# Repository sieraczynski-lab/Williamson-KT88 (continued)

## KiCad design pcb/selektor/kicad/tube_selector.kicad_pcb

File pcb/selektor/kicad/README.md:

# TubeSel v0.5: selektor 4 wejść + drabinka przekaźnikowa 63 dB + sterownik I²C

Projekt KiCad 8 (otwiera się też w KiCad 9 i nowszych).

## Zawartość
- `tube_selector.kicad_pro`: projekt (klasy sieci Audio 0,4 mm / Coil 0,3 mm)
- `tube_selector.kicad_sch`: schemat (A3)
- `tube_selector.kicad_pcb`: płytka 96 × 74 mm, 2 warstwy, elementy rozmieszczone, strefy mas na obu warstwach, **bez ścieżek**
- `TubeSel.kicad_sym` + `sym-lib-table`: biblioteka symboli projektu
- `TubeSel.pretty` + `fp-lib-table`: footprint modułu DC-DC
- `BOM.csv`: lista elementów z numerami LCSC (separator `;`)
- `JLCPCB_BOM.csv`: BOM w formacie JLCPCB do zamówienia montażu (tylko elementy SMD)
- `LCSC_zamowienie.csv`: komplet elementów do samodzielnego montażu (2 płytki + zapas, ze złączami JST) do wgrania w narzędziu BOM na lcsc.com
- Podgląd schematu i rozmieszczenia: [`selektor_rozmieszczenie.png`, `selektor_schemat.png`](../)
- Pełna dokumentacja: [`docs/soloist/11-selektor.md`](../../../docs/soloist/11-selektor.md)
- Pliki projektu wygenerował skrypt `narzedzia/selektor/gen.py`. **Po rozpoczęciu trasowania w KiCadzie źródłem prawdy są pliki KiCad.** Ponowne uruchomienie generatora (`narzedzia/selektor/gen.py`) nadpisze ścieżki (zobacz [`narzedzia/selektor/README.md`](../../../narzedzia/selektor/README.md)).

## Układ
- **Selektor K1–K4:** COM = wejście, NO = wspólna szyna, NC = 1 kΩ do masy.
- **Drabinka K5–K10:** bity 1/2/4/8/16/32 dB, impedancja ok. 10 kΩ (9,6–10,8 kΩ), rezystory cienkowarstwowe 0,1% w wartościach dostępnych w JLCPCB/LCSC. Cewka ON = stopień tłumi. Błąd tłumienia ≤ 0,21 dB dla wszystkich 64 kodów (symulacja); kanały L i R mają identyczne wartości.

| Bit | Rs | Rp |
|---|---|---|
| −1 dB | 1,10k | 80,6k |
| −2 dB | 2,00k | 32,4k |
| −4 dB | 3,75k | 17,4k |
| −8 dB | 6,20k | 6,81k |
| −16 dB | 9,10k | 2,00k |
| −32 dB | 10,0k | 270R |
- **R33/R34 10 kΩ:** terminator, wymagany do poprawnych tłumień.
- **K11 mute (fail-safe):** bez prądu cewki wyjście jest zwarte do masy. Dźwięk dopiero po załączeniu K11.
- **Sterownik:** U1 MCP23017 (I²C) → U2, U3 ULN2803 (UTC ULN2803G-S18-R, LCSC C33924; dowolny ULN2803 w SOIC-18 300 mil pasuje) → cewki. Diody gaszące są w ULN2803 (COM → +12 V).

| Wyjście MCP23017 | Przekaźnik | Funkcja |
|---|---|---|
| GPA0–GPA3 | K1–K4 | wejście 1–4 |
| GPA4–GPA7 | K5–K8 | −1, −2, −4, −8 dB |
| GPB0–GPB1 | K9–K10 | −16, −32 dB |
| GPB2 | K11 | mute (H = dźwięk) |
| GPB3–GPB7 | — | wolne |

Wyjście w stanie H = cewka załączona.

- **Zasilanie:** płytka potrzebuje tylko +12 V. 3,3 V dla MCP23017 i pull-upów I²C daje moduł DC-DC U4 (wersja 3,3 V; pinout 1 −IN, 2 +IN, 3 OUT+, 4 OUT−; rozstaw 14,17 × 8,24 mm). Pobór z 3,3 V to kilka mA.
- **J6 (JST XH 6p) do ESP32:** 1 +12 V, 2 DGND, 3 n/c, 4 SDA, 5 SCL, 6 DGND. Pin 3 celowo nie jest podłączony: nie łącz 3,3 V z ESP32 z 3,3 V tej płytki (dwa źródła napięcia).
- **Adres I²C:** SJ1–SJ3 otwarte = **0x20**. Zwarcie SJn ustawia bit An (0x20–0x27). Jeśli na tej samej magistrali jest drugi MCP23017 (np. od przekaźników biasu), ustaw tu inny adres.
- **Pull-upy I²C 4,7 kΩ (R36, R37)** są na płytce. Jeśli ESP32 też ma swoje, nic się nie stanie.

## Masy
- **GND (audio)** i **DGND (cyfrowa)** to osobne sieci i osobne strefy miedzi. DGND zajmuje dolny pas płytki pod układami scalonymi.
- **R41 (0 Ω, domyślnie nie montować)** łączy je w jednym punkcie. Zostaw puste, jeśli masa ESP32 łączy się z masą wzmacniacza w gwieździe gdzie indziej (tak jest najlepiej). Zmontuj tylko wtedy, gdy DGND nie ma innego połączenia z masą wzmacniacza.
- **R35 (0 Ω, DNP)** łączy masę audio z obudową przez MH1.

## Do sprawdzenia przed zamówieniem
1. **Biegunowość cewki G6K-2F-Y: potwierdzona.** Pin 1 = +12 V, pin 8 = do ULN2803. Przy lutowaniu ustaw znacznik pinu 1 na obudowie przekaźnika zgodnie ze znacznikiem na sitodruku; odwrotnie wlutowany polaryzowany przekaźnik nie zadziała.
2. Kolejność pinów kabli audio na J1–J5 (sitodruk „R G L”).
3. **Footprint modułu DC-DC** odwzorowałem ze zrzutu ekranu: otwory 1,0 mm, pady 2,2 mm, obrys 17,6 × 12,2 mm. Zmierz suwmiarką swój moduł (średnicę pinów i obrys) albo podmień footprint na własny.
4. Moduł DC-DC przy obciążeniu kilku mA zwykle pracuje w trybie impulsowym (burst). Jeśli w głośnikach pojawi się cichy szum lub „ćwierkanie”, pomoże dławik/ferryt w linii +3V3 albo zastąpienie modułu stabilizatorem 78L33.

## Kroki w KiCadzie
1. Otwórz `tube_selector.kicad_pro`.
2. Schemat: Inspect → Electrical Rules Checker.
3. PCB: Tools → Update PCB from Schematic (powinno nie wykryć zmian), poprowadź ścieżki (ręcznie lub wtyczką Freerouting), naciśnij **B** (wypełnienie stref) i uruchom DRC.

## Wskazówki do trasowania
- Tor audio na warstwie TOP, krótko; BOTTOM w części audio w miarę możliwości jako ciągła masa.
- Linie cewek (ULN → przekaźniki) i +12 V prowadź z dala od wejść, najlepiej prostopadle do ścieżek audio.
- Żadna ścieżka cyfrowa (SDA, SCL, DRV) nie powinna wchodzić w część audio.
- Kanały L (pady po prawej stronie przekaźników) i R (po lewej) rozdzielaj masą.

## Sterowanie
Zmiana głośności: najpierw ZAŁĄCZ nowe bity, odczekaj ~5 ms, potem WYŁĄCZ zbędne. Przejście zawsze idzie przez stan cichszy.
Po starcie MCP23017 ma wszystkie piny jako wejścia, więc wszystkie przekaźniki są wyłączone: wejście 1 niewybrane, tłumienie 0 dB i **mute aktywny**. Odblokowanie dźwięku następuje dopiero, gdy firmware ustawi wejście, głośność i GPB2 = 1.

## Montaż w JLCPCB
- `JLCPCB_BOM.csv` zawiera wszystkie elementy SMD z numerami LCSC (stan magazynu sprawdzony 22.10.2026). Plik pozycji (CPL) wygeneruj w KiCadzie po poprowadzeniu ścieżek: File → Fabrication Outputs → Component Placement (.pos), format CSV, jednostki mm.
- Złącza JST (J1–J6) i moduł DC-DC (U4) są przewlekane, więc najprościej przylutować je samemu.
- R35 i R41 (0 Ω, opcjonalne) są poza BOM-em JLCPCB.
- **Przed zatwierdzeniem zamówienia sprawdź w podglądzie JLCPCB orientację każdego przekaźnika i układu scalonego** (znacznik pinu 1). Obrócony G6K nie zadziała.

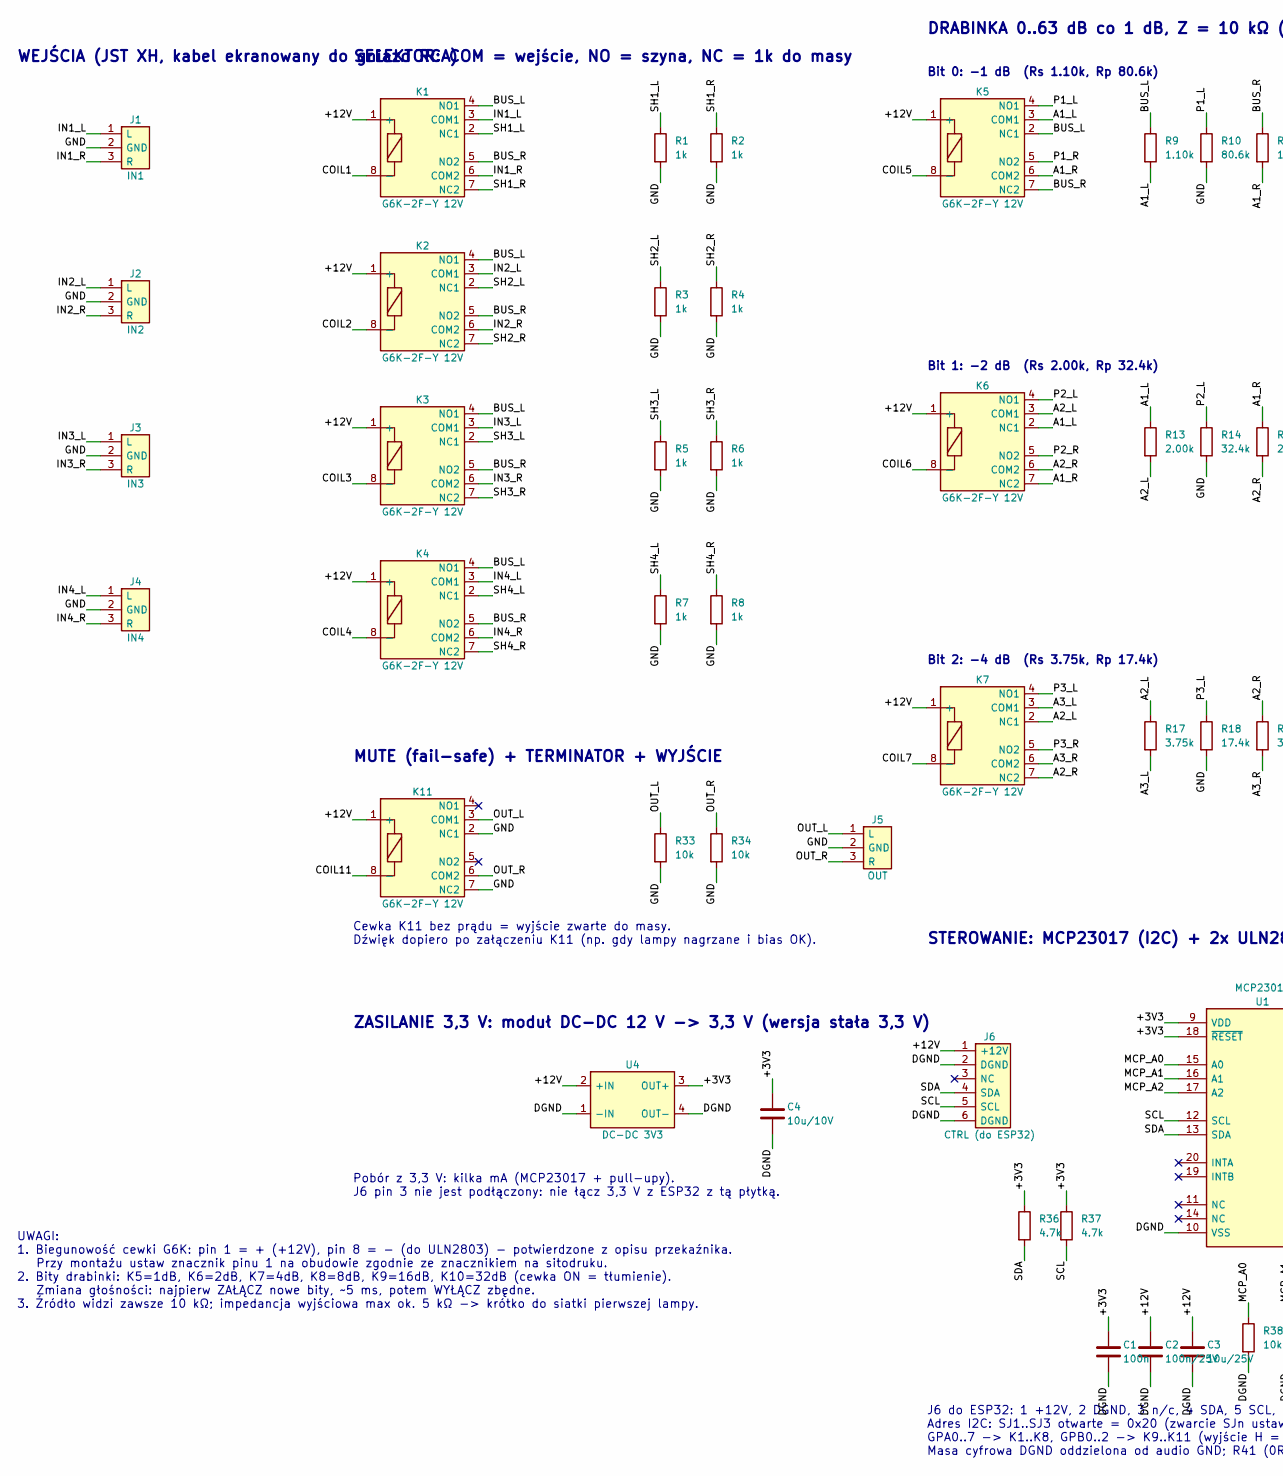
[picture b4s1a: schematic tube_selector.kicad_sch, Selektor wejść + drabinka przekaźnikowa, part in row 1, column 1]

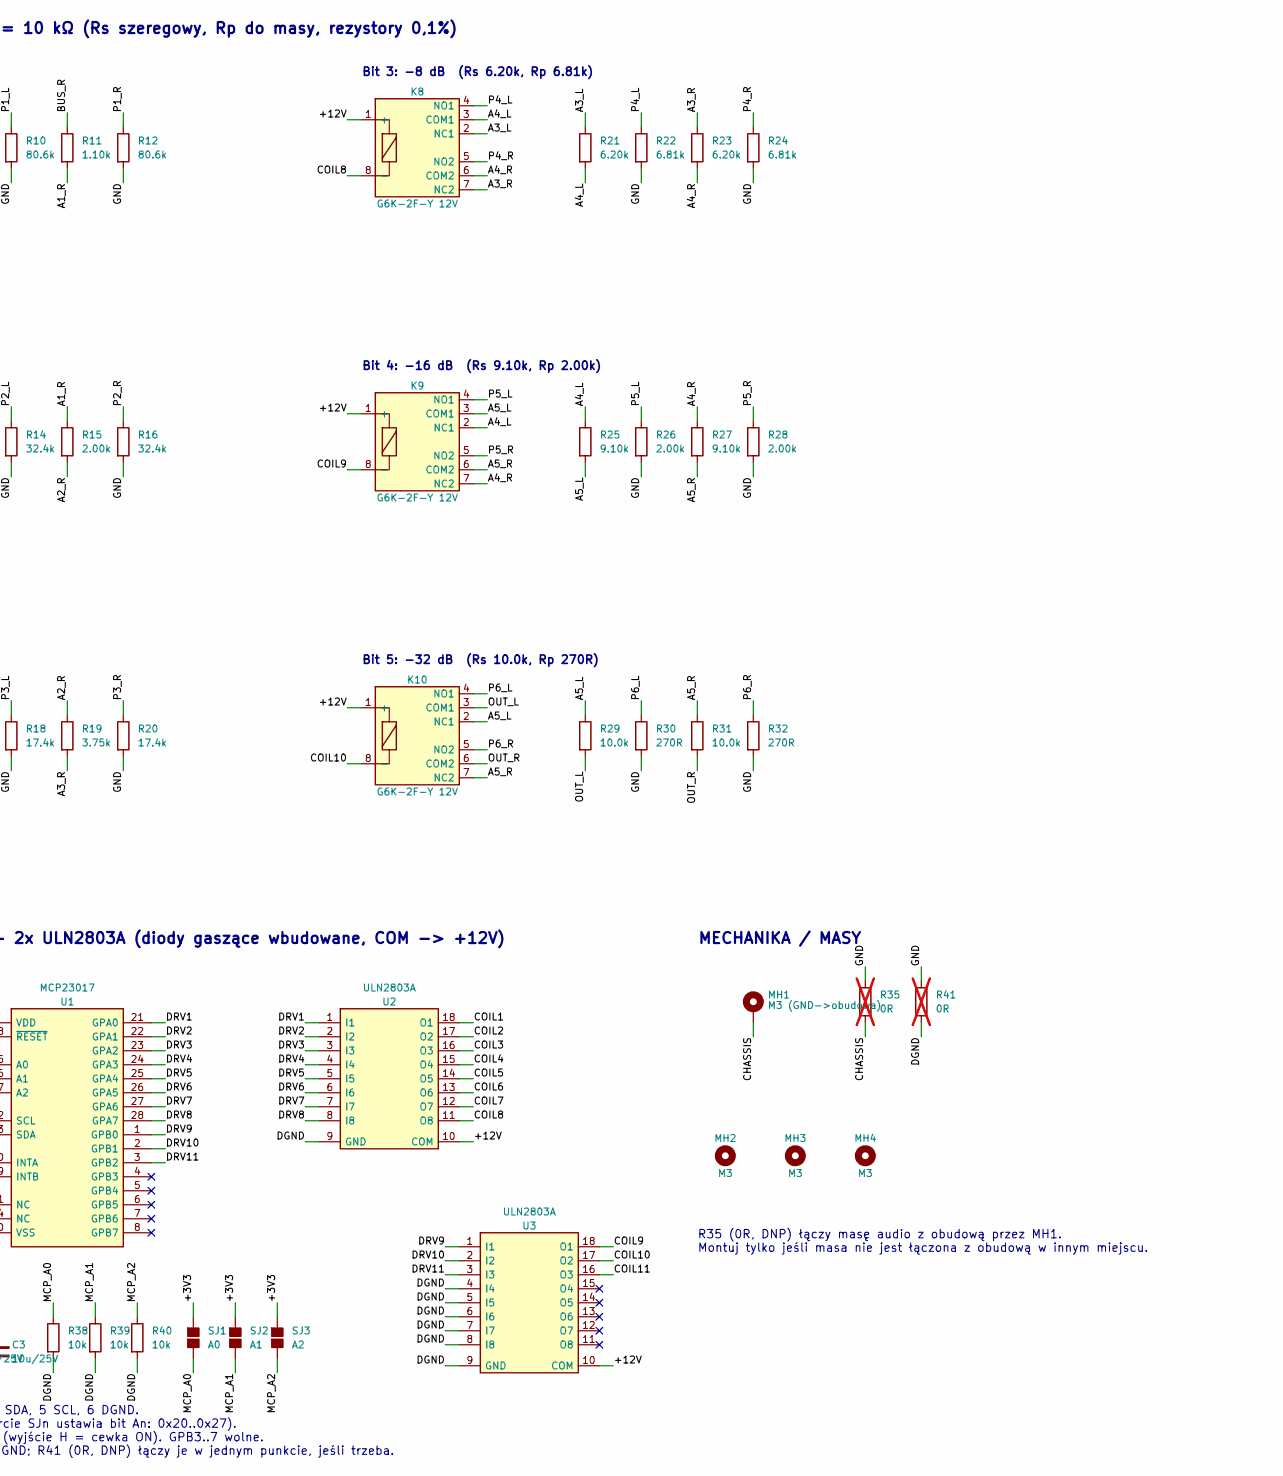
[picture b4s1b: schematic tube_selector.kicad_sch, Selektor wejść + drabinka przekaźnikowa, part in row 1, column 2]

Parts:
C1: 100n; C_0805_2012Metric; MPN CC0805KRX7R9BB104; LCSC C49678
C2: 100n/25V; C_0805_2012Metric; MPN CC0805KRX7R9BB104; LCSC C49678
C3: 10u/25V; C_1206_3216Metric; MPN CL31A106KBHNNNE; LCSC C13585
C4: 10u/10V; C_1206_3216Metric; MPN CL31A106KBHNNNE; LCSC C13585
J1: IN1; JST_XH_B3B-XH-A_1x03_P2.50mm_Vertical
J2: IN2; JST_XH_B3B-XH-A_1x03_P2.50mm_Vertical
J3: IN3; JST_XH_B3B-XH-A_1x03_P2.50mm_Vertical
J4: IN4; JST_XH_B3B-XH-A_1x03_P2.50mm_Vertical
J5: OUT; JST_XH_B3B-XH-A_1x03_P2.50mm_Vertical
J6: CTRL (do ESP32); JST_XH_B6B-XH-A_1x06_P2.50mm_Vertical; MPN JST B6B-XH-A + wtyk XHP-6
K1, K2, K3, K4, K5, K6, K7, K8, K9, K10, K11: G6K-2F-Y 12V; Relay_DPDT_Omron_G6K-2F-Y; MPN G6K-2F-Y-TR DC12; LCSC C397192
MH1: M3 (GND->obudowa); MountingHole_3.2mm_M3_Pad
MH2, MH3, MH4: M3; MountingHole_3.2mm_M3
R1, R2, R3, R4, R5, R6, R7, R8: 1k; R_0805_2012Metric; Tolerancja 1%; MPN 0805W8F1001T5E; LCSC C17513
R9, R11: 1.10k; R_0805_2012Metric; Tolerancja 0.1%; MPN ERA6AEB112V; LCSC C473284
R10, R12: 80.6k; R_0805_2012Metric; Tolerancja 0.1%; MPN RT0805BRD0780K6L; LCSC C728657
R13, R15, R26, R28: 2.00k; R_0805_2012Metric; Tolerancja 0.1%; MPN PTFR0805B2K00P9; LCSC C479096
R14, R16: 32.4k; R_0805_2012Metric; Tolerancja 0.1%; MPN TR0805B32K4P0550Z; LCSC C149970
R17, R19: 3.75k; R_0805_2012Metric; Tolerancja 0.1%; MPN AR05BTB3751A010; LCSC C374641
R18, R20: 17.4k; R_0805_2012Metric; Tolerancja 0.1%; MPN PTFR0805B17K4P9; LCSC C47115938
R21, R23: 6.20k; R_0805_2012Metric; Tolerancja 0.1%; MPN RT0805BRD076K2L; LCSC C326695
R22, R24: 6.81k; R_0805_2012Metric; Tolerancja 0.1%; MPN RT0805BRD076K81L; LCSC C728655
R25, R27: 9.10k; R_0805_2012Metric; Tolerancja 0.1%; MPN TC0525B9101T5G; LCSC C21571502
R29, R31: 10.0k; R_0805_2012Metric; Tolerancja 0.1%; MPN RT0805BRD0710KL; LCSC C110775
R30, R32: 270R; R_0805_2012Metric; Tolerancja 0.1%; MPN PTFR0805B270RN9; LCSC C351587
R33, R34: 10k; R_0805_2012Metric; Tolerancja 0.1%; MPN RT0805BRD0710KL; LCSC C110775
R35, R41: 0R; R_0805_2012Metric; not fitted
R36, R37: 4.7k; R_0805_2012Metric; Tolerancja 1%; MPN 0805W8F4701T5E; LCSC C17673
R38, R39, R40: 10k; R_0805_2012Metric; Tolerancja 1%; MPN 0805W8F1002T5E; LCSC C17414
SJ1: A0; SolderJumper-2_P1.3mm_Open_Pad1.0x1.5mm
SJ2: A1; SolderJumper-2_P1.3mm_Open_Pad1.0x1.5mm
SJ3: A2; SolderJumper-2_P1.3mm_Open_Pad1.0x1.5mm
U1: MCP23017; SOIC-28W_7.5x17.9mm_P1.27mm; MPN MCP23017-E/SO; LCSC C47023
U2, U3: ULN2803A; SOIC-18W_7.5x11.6mm_P1.27mm; MPN ULN2803G-S18-R (UTC); LCSC C33924
U4: DC-DC 3V3; DCDC_Mini_4pin_14.17x8.24mm; MPN Mini DC-DC step-down 3,3 V (pinout: 1 -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

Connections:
/+3V3: C1.1, C4.1, R36.1, R37.1, SJ1.1, SJ2.1, SJ3.1, U1.9 (VDD), U1.18 (~RESET), U4.3 (OUT+)
/+12V: C2.1, C3.1, J6.1 (+12V), K1.1 (+), K2.1 (+), K3.1 (+), K4.1 (+), K5.1 (+), K6.1 (+), K7.1 (+), K8.1 (+), K9.1 (+), K10.1 (+), K11.1 (+), U2.10 (COM), U3.10 (COM), U4.2 (+IN)
/A1_L: K5.3 (COM1), K6.2 (NC1), R9.2, R13.1
/A1_R: K5.6 (COM2), K6.7 (NC2), R11.2, R15.1
/A2_L: K6.3 (COM1), K7.2 (NC1), R13.2, R17.1
/A2_R: K6.6 (COM2), K7.7 (NC2), R15.2, R19.1
/A3_L: K7.3 (COM1), K8.2 (NC1), R17.2, R21.1
/A3_R: K7.6 (COM2), K8.7 (NC2), R19.2, R23.1
/A4_L: K8.3 (COM1), K9.2 (NC1), R21.2, R25.1
/A4_R: K8.6 (COM2), K9.7 (NC2), R23.2, R27.1
/A5_L: K9.3 (COM1), K10.2 (NC1), R25.2, R29.1
/A5_R: K9.6 (COM2), K10.7 (NC2), R27.2, R31.1
/BUS_L: K1.4 (NO1), K2.4 (NO1), K3.4 (NO1), K4.4 (NO1), K5.2 (NC1), R9.1
/BUS_R: K1.5 (NO2), K2.5 (NO2), K3.5 (NO2), K4.5 (NO2), K5.7 (NC2), R11.1
/CHASSIS: MH1.1, R35.2
/COIL1: K1.8 (-), U2.18 (O1)
/COIL2: K2.8 (-), U2.17 (O2)
/COIL3: K3.8 (-), U2.16 (O3)
/COIL4: K4.8 (-), U2.15 (O4)
/COIL5: K5.8 (-), U2.14 (O5)
/COIL6: K6.8 (-), U2.13 (O6)
/COIL7: K7.8 (-), U2.12 (O7)
/COIL8: K8.8 (-), U2.11 (O8)
/COIL9: K9.8 (-), U3.18 (O1)
/COIL10: K10.8 (-), U3.17 (O2)
/COIL11: K11.8 (-), U3.16 (O3)
/DGND: C1.2, C2.2, C3.2, C4.2, J6.2 (DGND), J6.6 (DGND), R38.2, R39.2, R40.2, R41.2, U1.10 (VSS), U2.9 (GND), U3.4 (I4), U3.5 (I5), U3.6 (I6), U3.7 (I7), U3.8 (I8), U3.9 (GND), U4.1 (-IN), U4.4 (OUT-)
/DRV1: U1.21 (GPA0), U2.1 (I1)
/DRV2: U1.22 (GPA1), U2.2 (I2)
/DRV3: U1.23 (GPA2), U2.3 (I3)
/DRV4: U1.24 (GPA3), U2.4 (I4)
/DRV5: U1.25 (GPA4), U2.5 (I5)
/DRV6: U1.26 (GPA5), U2.6 (I6)
/DRV7: U1.27 (GPA6), U2.7 (I7)
/DRV8: U1.28 (GPA7), U2.8 (I8)
/DRV9: U1.1 (GPB0), U3.1 (I1)
/DRV10: U1.2 (GPB1), U3.2 (I2)
/DRV11: U1.3 (GPB2), U3.3 (I3)
/GND: J1.2 (GND), J2.2 (GND), J3.2 (GND), J4.2 (GND), J5.2 (GND), K11.2 (NC1), K11.7 (NC2), R1.2, R2.2, R3.2, R4.2, R5.2, R6.2, R7.2, R8.2, R10.2, R12.2, R14.2, R16.2, R18.2, R20.2, R22.2, R24.2, R26.2, R28.2, R30.2, R32.2, R33.2, R34.2, R35.1, R41.1
/IN1_L: J1.1 (L), K1.3 (COM1)
/IN1_R: J1.3 (R), K1.6 (COM2)
/IN2_L: J2.1 (L), K2.3 (COM1)
/IN2_R: J2.3 (R), K2.6 (COM2)
/IN3_L: J3.1 (L), K3.3 (COM1)
/IN3_R: J3.3 (R), K3.6 (COM2)
/IN4_L: J4.1 (L), K4.3 (COM1)
/IN4_R: J4.3 (R), K4.6 (COM2)
/MCP_A0: R38.1, SJ1.2, U1.15 (A0)
/MCP_A1: R39.1, SJ2.2, U1.16 (A1)
/MCP_A2: R40.1, SJ3.2, U1.17 (A2)
/OUT_L: J5.1 (L), K10.3 (COM1), K11.3 (COM1), R29.2, R33.1
/OUT_R: J5.3 (R), K10.6 (COM2), K11.6 (COM2), R31.2, R34.1
/P1_L: K5.4 (NO1), R10.1
/P1_R: K5.5 (NO2), R12.1
/P2_L: K6.4 (NO1), R14.1
/P2_R: K6.5 (NO2), R16.1
/P3_L: K7.4 (NO1), R18.1
/P3_R: K7.5 (NO2), R20.1
/P4_L: K8.4 (NO1), R22.1
/P4_R: K8.5 (NO2), R24.1
/P5_L: K9.4 (NO1), R26.1
/P5_R: K9.5 (NO2), R28.1
/P6_L: K10.4 (NO1), R30.1
/P6_R: K10.5 (NO2), R32.1
/SCL: J6.5 (SCL), R37.2, U1.12 (SCL)
/SDA: J6.4 (SDA), R36.2, U1.13 (SDA)
/SH1_L: K1.2 (NC1), R1.1
/SH1_R: K1.7 (NC2), R2.1
/SH2_L: K2.2 (NC1), R3.1
/SH2_R: K2.7 (NC2), R4.1
/SH3_L: K3.2 (NC1), R5.1
/SH3_R: K3.7 (NC2), R6.1
/SH4_L: K4.2 (NC1), R7.1
/SH4_R: K4.7 (NC2), R8.1

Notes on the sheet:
WEJŚCIA (JST XH, kabel ekranowany do gniazd RCA)
SELEKTOR: COM = wejście, NO = szyna, NC = 1k do masy
DRABINKA 0..63 dB co 1 dB, Z = 10 kΩ (Rs szeregowy, Rp do masy, rezystory 0,1%)
Bit 0: -1 dB (Rs 1.10k, Rp 80.6k)
Bit 1: -2 dB (Rs 2.00k, Rp 32.4k)
Bit 2: -4 dB (Rs 3.75k, Rp 17.4k)
Bit 3: -8 dB (Rs 6.20k, Rp 6.81k)
Bit 4: -16 dB (Rs 9.10k, Rp 2.00k)
Bit 5: -32 dB (Rs 10.0k, Rp 270R)
MUTE (fail-safe) + TERMINATOR + WYJŚCIE
Cewka K11 bez prądu = wyjście zwarte do masy. Dźwięk dopiero po załączeniu K11 (np. gdy lampy nagrzane i bias OK).
ZASILANIE 3,3 V: moduł DC-DC 12 V -> 3,3 V (wersja stała 3,3 V)
Pobór z 3,3 V: kilka mA (MCP23017 + pull-upy). J6 pin 3 nie jest podłączony: nie łącz 3,3 V z ESP32 z tą płytką.
STEROWANIE: MCP23017 (I2C) + 2x ULN2803A (diody gaszące wbudowane, COM -> +12V)
J6 do ESP32: 1 +12V, 2 DGND, 3 n/c, 4 SDA, 5 SCL, 6 DGND. Adres I2C: SJ1..SJ3 otwarte = 0x20 (zwarcie SJn ustawia bit An: 0x20..0x27). GPA0..7 -> K1..K8, GPB0..2 -> K9..K11 (wyjście H = cewka ON). GPB3..7 wolne. Masa cyfrowa DGND oddzielona od audio GND; R41 (0R, DNP) łączy je w jednym punkcie, jeś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
MECHANIKA / MASY
R35 (0R, DNP) łączy masę audio z obudową przez MH1. Montuj tylko jeśli masa nie jest łączona z obudową w innym miejscu.
UWAGI: 1. Biegunowość cewki G6K: pin 1 = + (+12V), pin 8 = - (do ULN2803) - potwierdzone z opisu przekaźnika. Przy montażu ustaw znacznik pinu 1 na obudowie zgodnie ze znacznikiem na sitodruku. 2. Bity drabinki: K5=1dB, K6=2dB, K7=4dB, K8=8dB, K9=16dB, K10=32dB (cewka ON = tłumienie). Zmiana głośno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

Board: 2 copper layers, 73 parts (0 on the bottom side), 74 nets, no tracks yet.

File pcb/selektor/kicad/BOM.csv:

Ilość;Referencje;Wartość;Tolerancja;Obudowa;LCSC;Uwagi
1;C1;100n;;C_0805_2012Metric;C49678;X7R
1;C2;100n/25V;;C_0805_2012Metric;C49678;X7R
1;C3;10u/25V;;C_1206_3216Metric;C14860;X5R/X7R
1;C4;10u/10V;;C_1206_3216Metric;C14860;X5R/X7R
5;J1, J2, J3, J4, J5;JST_XH_B3B-XH-A_1x03_P2.50mm_Vertical;;JST_XH_B3B-XH-A_1x03_P2.50mm_Vertical;;JST B3B-XH-A + wtyk XHP-3 (IN1..IN4, OUT)
1;J6;CTRL (do ESP32);;JST_XH_B6B-XH-A_1x06_P2.50mm_Vertical;;JST B6B-XH-A + wtyk XHP-6
11;K1, K2, K3, K4, K5, K6, K7, K8, K9, K10, K11;G6K-2F-Y 12V;;Relay_DPDT_Omron_G6K-2F-Y;C397192;G6K-2F-Y-TR DC12
8;R1, R2, R3, R4, R5, R6, R7, R8;1k;1%;R_0805_2012Metric;C17513;0805W8F1001T5E
2;R9, R11;1.10k;0.1%;R_0805_2012Metric;C473284;ERA6AEB112V
2;R10, R12;80.6k;0.1%;R_0805_2012Metric;C728657;RT0805BRD0780K6L
4;R13, R15, R26, R28;2.00k;0.1%;R_0805_2012Metric;C479096;PTFR0805B2K00P9
2;R14, R16;32.4k;0.1%;R_0805_2012Metric;C149970;TR0805B32K4P0550Z
2;R17, R19;3.75k;0.1%;R_0805_2012Metric;C374641;AR05BTB3751A010
2;R18, R20;17.4k;0.1%;R_0805_2012Metric;C47115938;PTFR0805B17K4P9
2;R21, R23;6.20k;0.1%;R_0805_2012Metric;C326695;RT0805BRD076K2L
2;R22, R24;6.81k;0.1%;R_0805_2012Metric;C728655;RT0805BRD076K81L
2;R25, R27;9.10k;0.1%;R_0805_2012Metric;C21571502;TC0525B9101T5G
2;R29, R31;10.0k;0.1%;R_0805_2012Metric;C110775;RT0805BRD0710KL
2;R30, R32;270R;0.1%;R_0805_2012Metric;C351587;PTFR0805B270RN9
2;R33, R34;10k;0.1%;R_0805_2012Metric;C110775;RT0805BRD0710KL
0;R35, R41;0R;;R_0805_2012Metric;;NIE MONTOWAĆ (opcja)
2;R36, R37;4.7k;1%;R_0805_2012Metric;C17673;0805W8F4701T5E
3;R38, R39, R40;10k;1%;R_0805_2012Metric;C17414;0805W8F1002T5E
1;SJ1;A0;;SolderJumper-2_P1.3mm_Open_Pad1.0x1.5mm;;
1;SJ2;A1;;SolderJumper-2_P1.3mm_Open_Pad1.0x1.5mm;;
1;SJ3;A2;;SolderJumper-2_P1.3mm_Open_Pad1.0x1.5mm;;
1;U1;MCP23017;;SOIC-28W_7.5x17.9mm_P1.27mm;C47023;MCP23017-E/SO
2;U2, U3;ULN2803A;;SOIC-18W_7.5x11.6mm_P1.27mm;C33924;ULN2803G-S18-R (UTC)
1;U4;DC-DC 3V3;;DCDC_Mini_4pin_14.17x8.24mm;;Mini DC-DC step-down 3,3 V (pinout: 1 -IN, 2 +IN, 3 OUT+, 4 OUT-)

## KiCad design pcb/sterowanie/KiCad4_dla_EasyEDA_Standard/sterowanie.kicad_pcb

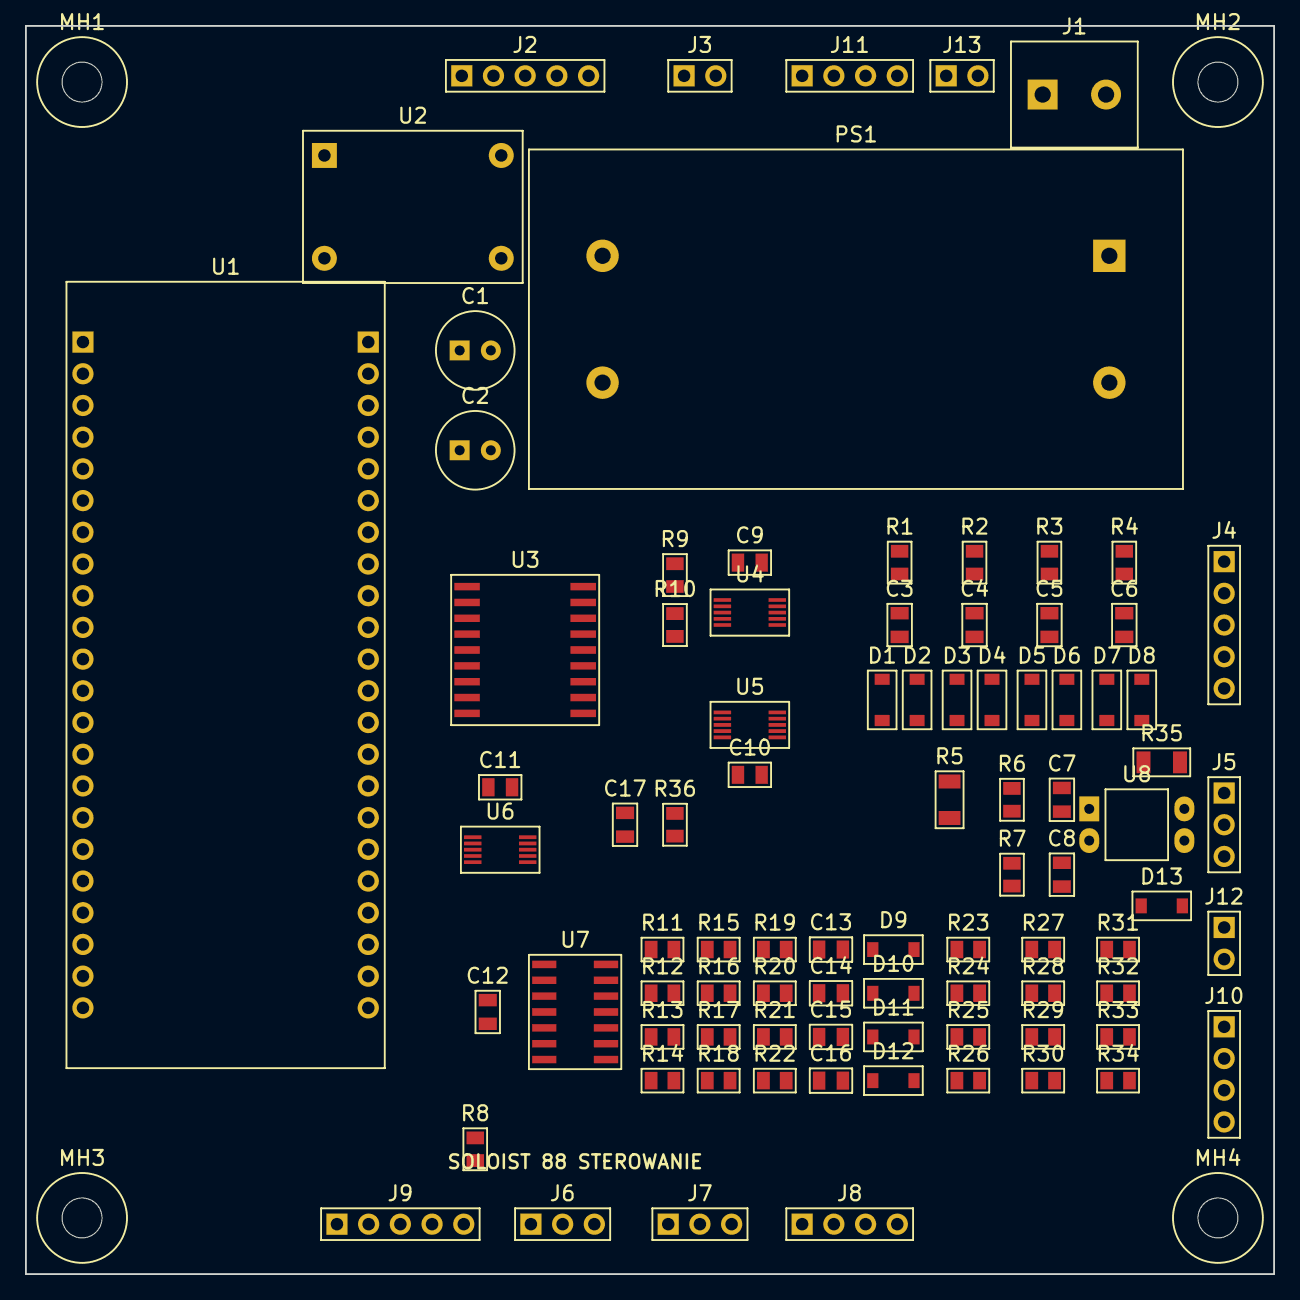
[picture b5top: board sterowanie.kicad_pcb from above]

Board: 2 copper layers, 100.0 x 100.0 mm, 92 parts (0 on the bottom side), 68 nets, no tracks yet.

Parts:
C1: 100u/25V; CP_Radial_D6.3_P2.5
C2: 100u/16V; CP_Radial_D6.3_P2.5
C3, C4, C5, C6, C7, C8: 1u; C_0805_2012Metric_V
C9, C10, C11: 100n; C_0805_2012Metric
C12, C17: 100n; C_0805_2012Metric_V
C13, C14, C15, C16: 1u; C_0805_2012Metric
D1, D2, D3, D4, D5, D6, D7, D8: 1N4148W; D_SOD-123_V
D9, D10, D11, D12, D13: 1N4148W; D_SOD-123
J1: 230V_IN; TerminalBlock_1x02_P5.08
J2: RELAY; PinHeader_1x05_P2.54_H
J3: MUTE; PinHeader_1x02_P2.54_H
J4: IK; PinHeader_1x05_P2.54
J5: SENSE; PinHeader_1x03_P2.54
J6: DS18B20; PinHeader_1x03_P2.54_H
J7: IR; PinHeader_1x03_P2.54_H
J8: WYSWIETLACZ; PinHeader_1x04_P2.54_H
J9: ENKODER; PinHeader_1x05_P2.54_H
J10: BIAS_KOR; PinHeader_1x04_P2.54
J11: UL_TRIODA; PinHeader_1x04_P2.54_H
J12: TRIGGER; PinHeader_1x02_P2.54
J13: GLOSNIKI; PinHeader_1x02_P2.54_H
MH1, MH2, MH3, MH4: M3; MountingHole_M3
PS1: IRM-15-12; MeanWell_IRM-15_approx
R1, R2, R3, R4, R6, R7, R36: 10k; R_0805_2012Metric_V
R5: 330k 1206; R_1206_3216Metric_V
R8, R9, R10: 4k7; R_0805_2012Metric_V
R11, R12, R13, R14, R19, R20, R21, R22: 10k; R_0805_2012Metric
R15, R16, R17, R18: 20k; R_0805_2012Metric
R23, R24, R25, R26: 68k; R_0805_2012Metric
R27, R28, R29, R30: 33k; R_0805_2012Metric
R31, R32, R33, R34: 1k; R_0805_2012Metric
R35: 1k 1206; R_1206_3216Metric
U1: ESP32-S3-DevKitC-1
U2: DC-DC 5V mini; DCDC_5V_mini_14.17x8.24
U3: ULN2803G-S18-R; SOIC-18W_7.5x11.6mm_P1.27mm
U4: ADS1115IDGSR 0x48; MSOP-10_3x3mm_P0.5mm
U5: ADS1115IDGSR 0x49; MSOP-10_3x3mm_P0.5mm
U6: MCP4728-E/UN; MSOP-10_3x3mm_P0.5mm
U7: LM324DR; SOIC-14_3.9x8.7mm_P1.27mm
U8: PC817; DIP-4_W7.62

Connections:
3V3: C9.1, C10.1, C11.1, D2.1, D4.1, D6.1, D8.1, J6.1, J7.1, J8.1, R6.2, R8.1, R9.1, R10.1, R36.1, U1.L1, U1.L2, U4.8, U5.1, U5.5, U5.8, U6.1
+5V: C2.1, U1.L21, U2.3
+12V: C1.1, C12.1, J2.1, J3.1, J11.1, J11.3, J13.1, PS1.4, U2.2, U3.10, U7.4
BI_L1: J10.1, R31.2
BI_L2: J10.2, R32.2
BI_R1: J10.3, R33.2
BI_R2: J10.4, R34.2
BTN: J9.4, U1.L9
DACF_L1: C13.1, R19.2, U7.3
DACF_L2: C14.1, R20.2, U7.5
DACF_R1: C15.1, R21.2, U7.10
DACF_R2: C16.1, R22.2, U7.12
DAC_L1: R19.1, U6.6
DAC_L2: R20.1, U6.7
DAC_R1: R21.1, U6.8
DAC_R2: R22.1, U6.9
DQ: J6.2, R8.2, U1.L4
DRV1: U1.L16, U3.1
DRV2: U1.L17, U3.2
DRV3: U1.L18, U3.3
DRV4: U1.L19, U3.4
DRV5: U1.L20, U3.5
DRV6: U1.L10, U3.6
DRV7: U1.L11, U3.7
ENC_A: J9.1, U1.L6
ENC_B: J9.2, U1.L7
ENC_SW: J9.3, U1.L8
FB_L1: R11.1, R15.2, U7.2
FB_L2: R12.1, R16.2, U7.6
FB_R1: R13.1, R17.2, U7.9
FB_R2: R14.1, R18.2, U7.13
GND: C1.2, C2.2, C3.2, C4.2, C5.2, C6.2, C7.2, C8.2, C9.2, C10.2, C11.2, C12.2, C13.2, C14.2, C15.2, C16.2, C17.2, D1.2, D3.2, D5.2, D7.2, D9.2, D10.2, D11.2, D12.2, J4.5, J5.3, J6.3, J7.3, J8.2, J9.5, PS1.3, R11.2, R12.2, R13.2, R14.2, U1.L22, U1.R1, U1.R21, U1.R22, U2.1, U2.4, U3.8, U3.9, U4.1, U4.3, U5.3, U6.4, U6.10, U7.11, U8.3
HV_F: C8.1, R7.2, U5.6
HV_SENSE: J5.2, R7.1
IK_L1: J4.1, R1.1
IK_L1F: C3.1, D1.1, D2.2, R1.2, U4.4
IK_L2: J4.2, R2.1
IK_L2F: C4.1, D3.1, D4.2, R2.2, U4.5
IK_R1: J4.3, R3.1
IK_R1F: C5.1, D5.1, D6.2, R3.2, U4.6
IK_R2: J4.4, R4.1
IK_R2F: C6.1, D7.1, D8.2, R4.2, U4.7
IR: J7.2, U1.L5
L_PS: J1.1, PS1.1
MUTE: J3.2, U3.14
N_PS: J1.2, PS1.2
OA_L1: D9.1, R15.1, R23.1, U7.1
OA_L2: D10.1, R16.1, R24.1, U7.7
OA_R1: D11.1, R17.1, R25.1, U7.8
OA_R2: D12.1, R18.1, R26.1, U7.14
OPTO_A: D13.1, R35.2, U8.1
RLY1: J2.2, U3.18
RLY2: J2.3, U3.17
RLY3: J2.4, U3.16
RLY4: J2.5, U3.15
RLY_SPK: J13.2, U3.12
RLY_UL: J11.2, J11.4, U3.13
SCL: J8.3, R10.2, U1.L15, U4.10, U5.10, U6.2
SDA: J8.4, R9.2, U1.L12, U4.9, U5.9, U6.3
S_L1: R23.2, R27.1, R31.1
S_L2: R24.2, R28.1, R32.1
S_R1: R25.2, R29.1, R33.1
S_R2: R26.2, R30.1, R34.1
TRIG_IN: C17.1, R36.2, U1.R4, U8.4
TRIG_N: D13.2, J12.2, U8.2
TRIG_P: J12.1, R35.1
VBIAS: J5.1, R5.1, R27.2, R28.2, R29.2, R30.2
VB_F: C7.1, R5.2, R6.1, U5.4

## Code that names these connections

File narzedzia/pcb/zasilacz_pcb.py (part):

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        ("R2", "100R 10W", "R", ["HT_K3", "HT_IN"], g_ht, "R_IN: udar ladowania kondensatorow Onyxa ok. 5 A"),
        ("K4", "G2RL-2-DC12", "RELAY_G2RL", {"1": "+12V", "8": "RLY4", "3": "HT_K3", "6": "HT_K3", "4": "HT_IN", "5": "HT_IN", "2": None, "7": None}, g_ht,
         "bocznik R_IN (+1,5 s); 2 styki rownolegle"),
        ("J8", "HT_L", "CONN_2", ["HT_IN", "HT_B"], g_ht, "zlacze srubowe 7,62 mm: do Onyx J103 (1 -> pin 1, 2 -> pin 2)"),
        ("J9", "HT_R", "CONN_2", ["HT_IN", "HT_B"], g_ht, "zlacze srubowe 7,62 mm: do Onyx J203"),
        # ---- bias ----
        ("J10", "S4_IN", "CONN_2", ["B_AC1", "B_AC2"], g_b, "zlacze srubowe: S4 58 V z TR1"),
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        ("R4", "1M 1% 1600V", "R", ["HVS1", "HVS2"], g_s, ""),
        ("R5", "1M 1% 1600V", "R", ["HVS2", "HV_SENSE"], g_s, ""),
        ("R6", "15k 1%", "R", ["HV_SENSE", "GND"], g_s, "metalizowany 1 %; ok. 2,3 V przy 465 V"),
        ("J14", "HV_SENSE", "PAD", ["HV_SENSE"], g_s, "do sterowania J5 pin 2"),
        ("J15", "GND_ONYX", "PAD", ["GND"], g_c, "masa: do gwiazdy na plytce Onyxa (minus C120)"),
        ("J18", "GND_STER", "PAD", ["GND"], g_c, "masa pomiaru: do sterowania J5"),
        # ---- LED HV ----
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        ("R8", "220k 1W", "R", ["LED_M", "LED_A"], g_l, ""),
        ("D1", "LED HV czerwona", "D", {"1": "GND", "2": "LED_A"}, g_l, "swieci, dopoki na plytce Onyxa jest napiecie; NIE ZASTEPUJE MIERNIKA"),
        # ---- cewki ----
        ("J16", "RELAY_A", "CONN_3", ["+12V", "RLY1", "RLY2"], g_r, "ze sterowania J2 piny 1,2,3"),
        ("J17", "RELAY_B", "CONN_3", ["+12V", "RLY3", "RLY4"], g_r, "ze sterowania J2 piny 1,4,5"),
        ("D2", "1N4148", "D", {"1": "+12V", "2": "RLY1"}, g_r, ""),
        ("D3", "1N4148", "D", {"1": "+12V", "2": "RLY2"}, g_r, ""),
        ("D4", "1N4148", "D", {"1": "+12V", "2": "RLY3"}, g_r, ""),
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
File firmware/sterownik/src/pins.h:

#pragma once
// Przydzial pinow plytki "sterowanie" (docs/10, rozdz. 2.1 i 2.2)

namespace pins {
constexpr int I2C_SDA = 8;
constexpr int I2C_SCL = 9;

// Wyjscia na ULN2803 (stan wysoki = cewka zalaczona)
constexpr int RLY_K1 = 10;     // K1: siec przez R_SS (zarzenie, bias)
constexpr int RLY_K2 = 11;     // K2: bypass R_SS
constexpr int RLY_K3 = 12;     // K3: anody przez R_IN
constexpr int RLY_K4 = 13;     // K4: bypass R_IN
constexpr int RLY_SOUND = 14;  // J3 -> K11 selektora (wariant 7.5b): aktywne = DZWIEK
constexpr int RLY_UL = 17;     // J11: 4 przekazniki UL/trioda, aktywne = trioda, bez pradu = UL
constexpr int RLY_SPK = 18;    // J13: kolumny, aktywne = lampa, bez pradu = Marantz

constexpr int TRIG_IN = 1;     // transoptor, 0 = 12 V triggera obecne
constexpr int ONEWIRE = 4;     // DS18B20 (etap 2)
constexpr int IR_RX = 5;       // TSOP38238 (etap 4)
constexpr int ENC_VOL_A = 6;   // enkoder glosnosci (etap 4)
constexpr int ENC_VOL_B = 7;
constexpr int ENC_VOL_SW = 15;
constexpr int BTN_POWER = 16;  // przycisk wlacz / czuwanie, zalozenie: zwiera do masy (sprawdzic na plytce)

// Nowe, prawa listwa DevKitC (etap 4 / 6)
constexpr int ENC_SEL_A = 21;
constexpr int ENC_SEL_B = 47;
constexpr int ENC_SEL_SW = 48;  // albo 38, zalezy od wersji DevKitC (dioda RGB)
constexpr int VU_L = 2;         // ADC1
constexpr int VU_R = 3;         // ADC1, strapping JTAG
}  // namespace pins
